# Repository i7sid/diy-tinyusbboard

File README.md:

# diy-tinyusbboard
Das DIY tinyUSBboard ist abgeleitet vom [tinyusbboard](https://github.com/tinyusbboard) und wurde für die Vorlesung ["DIY: Personal Fabrication"](http://www7.cs.fau.de/de/teaching/diy-2015w/) als Löttutorial entwickelt.

## In der Arduino IDE
Ab der Arduino IDE 1.6.4 kann man dieses Board mit der [Boards Manager URL](https://github.com/i7sid/diy-tinyusbboard/raw/master/Arduino/package_diy-tinyusbboard_index.json) hinzufügen.

Board Manager Link: `https://github.com/i7sid/diy-tinyusbboard/raw/master/Arduino/package_diy-tinyusbboard_index.json`

Zum Ätzen, Löten und ersten Programmieren besteht eine [Anleitung](https://github.com/i7sid/diy-tinyusbboard/raw/master/anleitung/anleitung.pdf).
### Arduino PIN-Belegung

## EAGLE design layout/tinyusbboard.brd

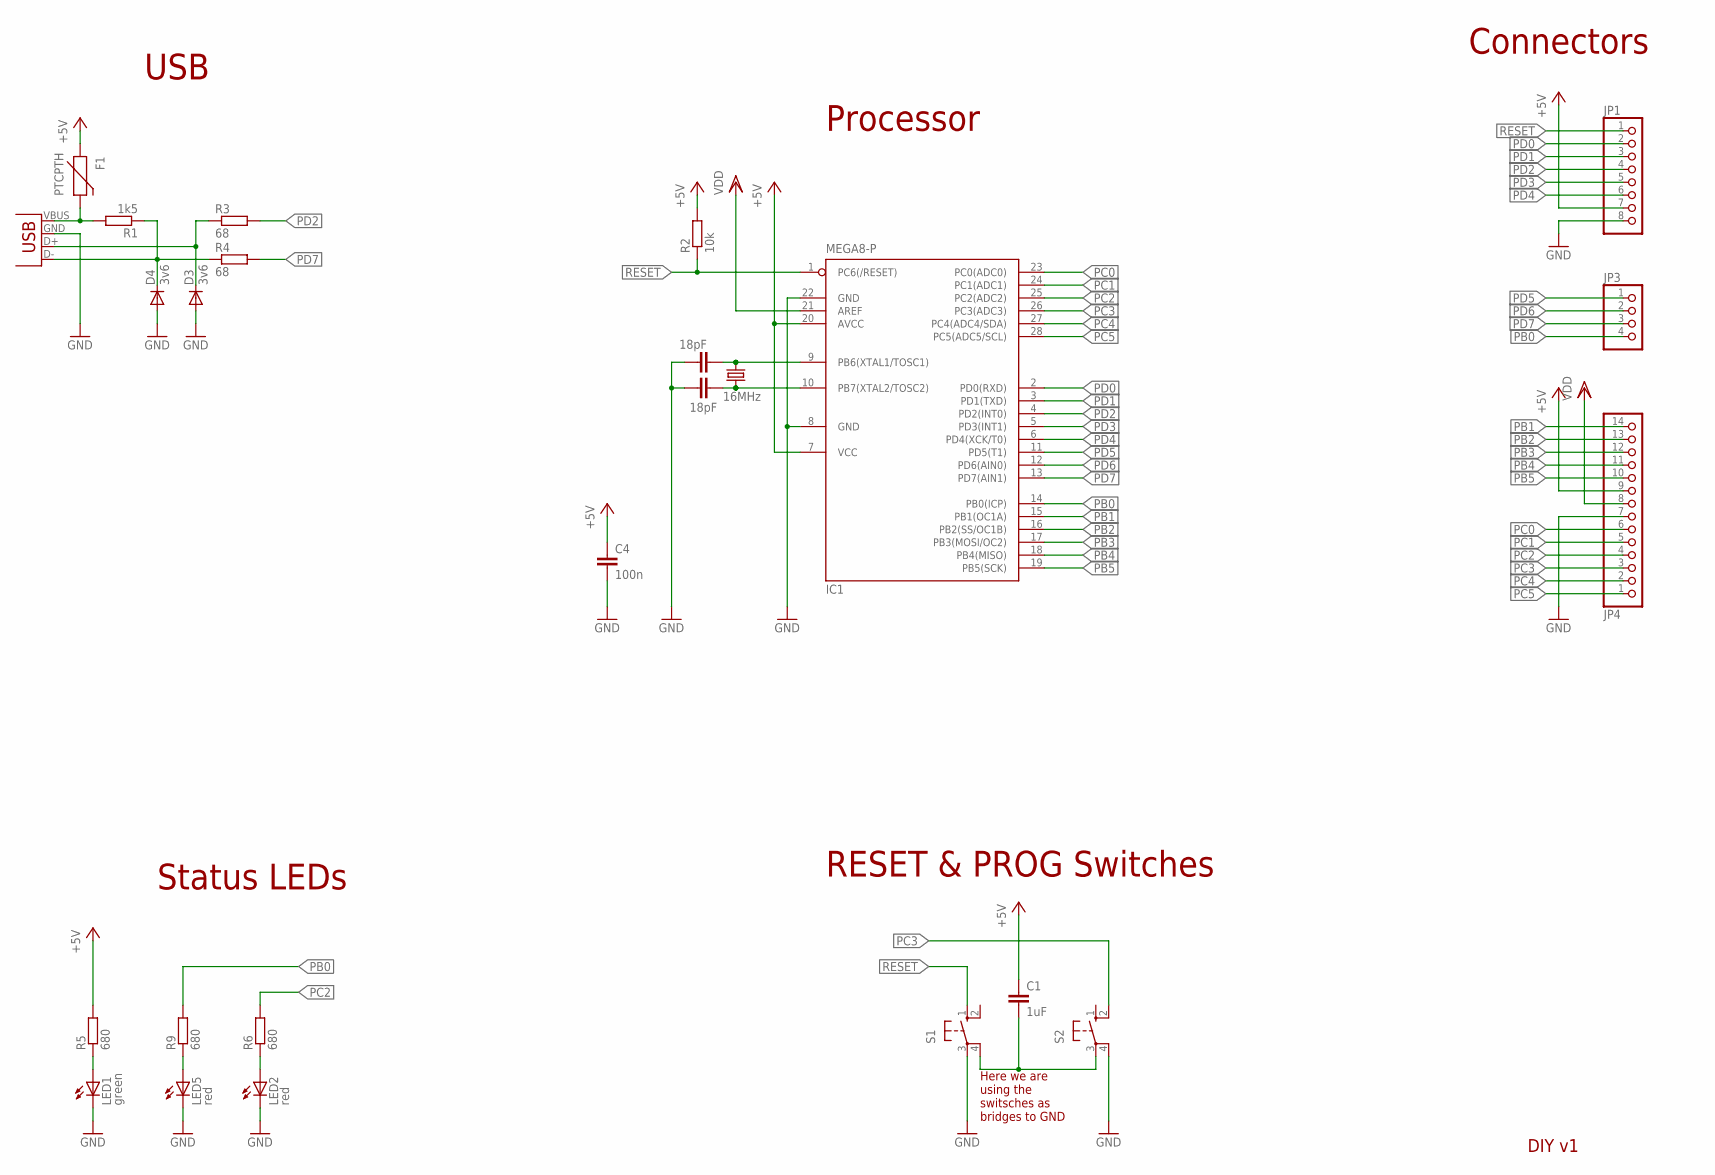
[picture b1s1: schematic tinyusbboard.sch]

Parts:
C1: 1uF; C0805
C2, C3: 18pF; C0805K
C4: 100n; C0805
D3, D4: 3v6; MINIMELF
F1: PTCPTH; PTC
IC1: MEGA8-P; DIL28-3
JP1: PINHD-1X8; 1X08
JP3: PINHD-1X4; 1X04
JP4: PINHD-1X14; 1X14
JP5: USB-A-H
LED1: green; CHIPLED_0805
LED2, LED5: red; CHIPLED_0805
Q1: 16MHz; HC49/S
R1: 1k5; M0805
R2: 10k; R1206
R3, R4: 68; M0805
R5, R6, R9: 680; R0805
S1, S2: 10-XX; B3F-10XX

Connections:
+5V: C1.1, C4.1, F1.P$1 (1), IC1.7 (VCC), IC1.20 (AVCC), JP1.7, JP4.9, R2.2, R5.2
D+: D3.C, JP5.D+ (D-), R3.1
D-: D4.C, JP5.D- (D+), R1.1, R4.1
GND: C2.2, C3.2, C4.2, D3.A, D4.A, IC1.8 (GND), IC1.22 (GND), JP1.8, JP4.7, JP5.GND (VBUS), LED1.C, LED2.C, LED5.C, S1.3, S2.4 (P1)
unnamed: F1.P$2 (2), JP5.VBUS (GND), R1.2
unnamed: LED1.A, R5.1
unnamed: C3.1, IC1.9 (PB6(XTAL1/TOSC1)), Q1.1
unnamed: C2.1, IC1.10 (PB7(XTAL2/TOSC2)), Q1.2
unnamed: LED5.A, R9.1
unnamed: LED2.A, R6.1
unnamed: C1.2, S1.4 (P1), S2.3
PB0: IC1.14 (PB0(ICP)), JP3.4, R9.2
PB1: IC1.15 (PB1(OC1A)), JP4.14
PB2: IC1.16 (PB2(SS/OC1B)), JP4.13
PB3: IC1.17 (PB3(MOSI/OC2)), JP4.12
PB4: IC1.18 (PB4(MISO)), JP4.11
PB5: IC1.19 (PB5(SCK)), JP4.10
PC0: IC1.23 (PC0(ADC0)), JP4.6
PC1: IC1.24 (PC1(ADC1)), JP4.5
PC2: IC1.25 (PC2(ADC2)), JP4.4, R6.2
PC3: IC1.26 (PC3(ADC3)), JP4.3, S2.2 (S1)
PC4: IC1.27 (PC4(ADC4/SDA)), JP4.2
PC5: IC1.28 (PC5(ADC5/SCL)), JP4.1
PD0: IC1.2 (PD0(RXD)), JP1.2
PD1: IC1.3 (PD1(TXD)), JP1.3
PD2: IC1.4 (PD2(INT0)), JP1.4, R3.2
PD3: IC1.5 (PD3(INT1)), JP1.5
PD4: IC1.6 (PD4(XCK/T0)), JP1.6
PD5: IC1.11 (PD5(T1)), JP3.1
PD6: IC1.12 (PD6(AIN0)), JP3.2
PD7: IC1.13 (PD7(AIN1)), JP3.3, R4.2
RESET: IC1.1 (PC6(/RESET)), JP1.1, R2.1, S1.1 (S)
VDD: IC1.21 (AREF), JP4.8

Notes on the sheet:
Status LEDs
Connectors
RESET & PROG Switches
DIY v1
Processor
USB
Here we are using the switsches as bridges to GND

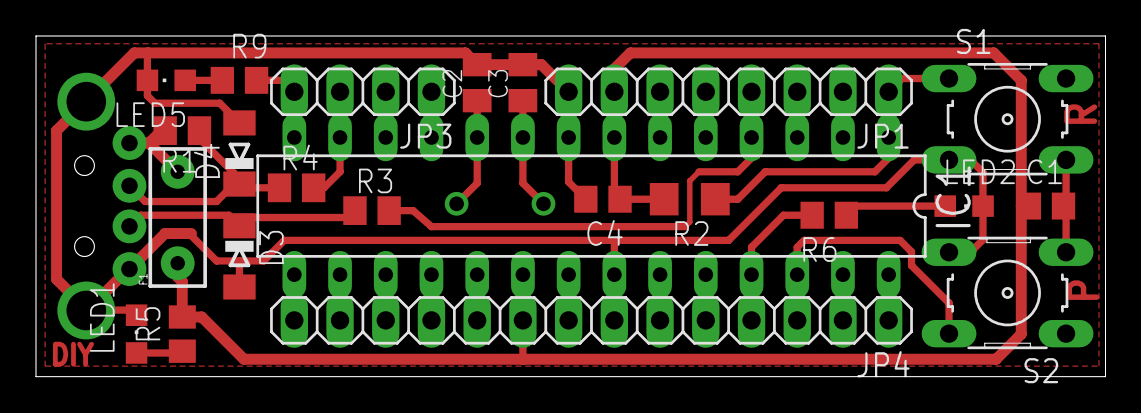
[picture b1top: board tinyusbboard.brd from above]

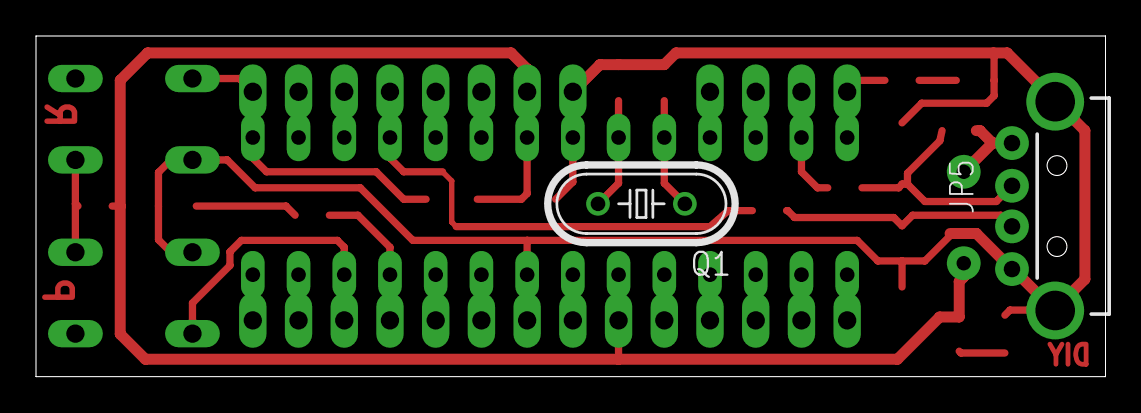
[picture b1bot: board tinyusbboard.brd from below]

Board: 2 copper layers, 59.4 x 18.9 mm, 25 parts (2 on the bottom side), 33 nets.

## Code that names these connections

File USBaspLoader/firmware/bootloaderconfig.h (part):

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    #define USB_CFG_INTPORT_BIT 2
  #endif
#endif
/* Not all devices have their INT0 on PD2.
 * Since "INT0" and "USB_CFG_DPLUS_BIT" should get the same signals,
 * map them to be ideally the same:
 * So abstract "USB_CFG_DPLUS_BIT" to this one here.
 */

#ifndef USB_CFG_DMINUS_BIT
  /* This is Revision 3 and later (where PD6 and PD7 were swapped */
  #define USB_CFG_DMINUS_BIT      7    /* Rev.2 and previous was 6 */
#endif
/* This is the bit number in USB_CFG_IOPORT where the USB D- line is connected.
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 * jumper is connected to this port
 */
#ifndef JUMPER_BIT
  /* Swaped JUMPER from PD6 to PC3 */
  #define JUMPER_BIT           3       /* rev3-smd was 3 */
#endif
/* 
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
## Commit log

2015-12-03 added exercise schematic
2015-12-06 added Bootloader for diy-tinyUSBboard
2015-12-07 added instructions
2015-12-07 added Arduino Archive
2015-12-07 added json for copy paste board install
2015-12-08 added instructions for use with Arduino IDE
2015-12-08 added first readme
2015-12-09 added copy paste link
2015-12-15 Updatet Anleitung nach Erfahrungen des ersten Tutorials
2015-12-20 switch demo added
2015-12-20 added some comments

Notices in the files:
USBaspLoader/firmware/bootloaderconfig.h:
Copyright: (c) 2007 by OBJECTIVE DEVELOPMENT Software GmbH
License: GNU GPL v2 (see License.txt)
parts and their libraries:
SparkFun: Licensing: CC v3.0 Share-Alike You are welcome to use this library for commercial purposes.
SparkFun-Connectors: Licensing: Creative Commons ShareAlike 4.0 International - https://creativecommons.org/licenses/by-sa/4.0
